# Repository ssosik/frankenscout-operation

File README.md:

# frankenscout-operation

Project files for a Trunk or Treat game: Arduino code, Kicad files, and general
design overview. Inspired by the game Operation with enhancements for multiple
faults before a game over, lots of gameplay sounds, and LED blinking patterns.

This was specifically for a Cub Scout Trunk or Treat event, so it's themed
around the 12 words of the Cub Scout Law: Trustworthy, Loyal, Helpful, Friendly,
Courteous, Kind, Obedient, Cheerful, Thrifty, Brave, Clean and Reverent.

## Components

- Arduino Nano: https://store.arduino.cc/products/arduino-nano
- MP3 Trigger: https://www.robertsonics.com/mp3-trigger
- Aux-in-compatible boombox speaker
- Custom PCB printed by PCBWay
- 3D printed bones
- 2x4s and 1/4" playwood (3'x4' playfield)
- Metal tongs + phone cord
- Metal HVAC foil tape for lining the edge of the bone boxes
- Big printout playfield
- random LEDs, wires, resistors, JST connectors, 74HC595 IC
- So much hot-glue

## Playthrough

LEDs quickly cycle through lighting up each of the 12 bone boxes one at a time,
randomly stopping on one.

Play a recording of one of our Scouts reciting the Scout Law word corresponding
to the lit up bone.

Start playing a randomly selected Halloween themed song.

The player uses the attached metal tongs to try to remove the lit up bone.

Each time the player touches the edge of the bone box, a randomly selected
warning sound is played. These sounds are recordings of our Scouts making spooky
sounds. Change the color of the nose to correspond to the warning level (green,
orange, blinking orange).

After playing the warning sound, resume playing the theme song.

If the player gets 3 warnings, the game is over. Turn the nose red and play a
short game over song. Start a new game.

If the player successfully removes the bone, trigger a separate switch to play
the win game song and have all the LEDs light up. Start a new game.

https://github.com/ssosik/frankenscout-operation/assets/11655703/48587010-1746-46a9-8444-a14359af3e6e

## Table

Nothing fancy, just some 2x4s screwed together. I added some legs to give some
space between the underside of the playfield and the ground below. Kids might
lean on the table, so make it strong.

## Playfield

1/4 inch plywood, roughly 3'x4'

## Picture

One of the other parents in our Den has access to a large color plot-printer at
work. I don't have any details on what it was.

I asked google to find me a picture in the appropriate theme, but I really
wanted to use something generated by Midjourney or Stable Diffusion.

## Cut-outs

Hope you're handy with a Jigsaw! I ended up cutting out wider holes on the
playfield, and then glued pieces to the underside with a more close-fitting bone
shape. These glued-on pieces are what form the edge of the bone boxes that are
crucial to the game. The inner edge of these holes is lined with metal foil tape
to complete the circuit through the metal tongs and back to the Arduino
interrupt pin.

The next time I do this I would consider 3D printing these pieces as well.

## Bone boxes

These were just roughly cut pieces of scrape 1/4 wood laminate, hot-glued
together. These don't really need to look nice, other than what can be seen
through the cut-outs from the top side of the play field.

I also hot-glued a small piece of stripboard with a few LEDs and a JST connector
into the corner of each bone box.

## Bones

One of the other parents in our Den did the 3D printings of the bones, so I
don't have the data files or other parameters for the prints. thingiverse.com
has so much to choose from.

## Electronics

The heart of this is an Arduino Nano.

It uses the Serial pins to talk to the MP3 Trigger.

The Nano only supports interrups on pins 2 and 3, so these are what I used for
the triggers for game faults and game wins.

I went overboard and used this as an opportunity to learn a bit about PCB
design, so I learned how to use Kicad to design the PCB and then ordered pieces
through PCBWay.

## Sounds

For music, I was able to find a good amount of stuff on the freemusicarchive.org
(e.g. Toccata and Fugue D Minor). With google, you can find so much more.

I used VLC and Audacity to convert these files so that the MP3 Trigger could
play them. I'm not sure if it was a bitrate thing or what, but some of the files
skipped during playback without convertion.

I just used my Mac to record the voices of our Scouts making spooky sounds and
reciting the words of the Scout Law. I used Audacity to cut up the audio files.

In the code I have a few separate start and stop indexes for the theme songs,
warn sounds, win songs, and lose songs. I use `random` to pick a random file in
the range between these indexes.

The MP3 Trigger use a micro SD card to for loading the MP3 files. These files
have a numeric prefix XXX that is used to index each file; i.e. a file named
`012-some-file.mp3` will be played when `t12` is sent over the Serial port to
the MP3 Trigger.

https://github.com/ssosik/frankenscout-operation/assets/11655703/ff72e206-2da6-4ab1-b68c-d1a4c78e1dd9

## Useful Links

- https://www.instructables.com/Multiplexing-with-Arduino-and-the-74HC595/
- https://docs.arduino.cc/tutorials/nano-every/uart
- https://learn.sparkfun.com/tutorials/mp3-trigger-hookup-guide-v24
- https://www.baldengineer.com/state-machine-with-enum-tutorial.html

## Improvements

- Use a magnetic switch (Normally Open) and magnets in the bones to trigger the
win events
- Normalize the sound files better to make the sound of our Scouts louder
- I'd like to add some kind of buzzer or solenoid popper to the game to give it
a bit more physical feedback

## Bugs

- The Arduino Nano that I'm using will temporarily ignore interrupt events every
so often, making the game seem unresponsive. After a bit of time, the interrupts
start working again, without a power cycle. I'm not sure what the source of this
is. I'm using Nano pins 2 and 3 in INPUT_PULLUP mode. If you have any ideas
please let me know!
- I'm not a C++ programmer, and coding in an event loop is tricky. There were
many bugs, and there are probably still a few.
- I ran out of time and wan't able to get the nose LEDs working properly. TODO

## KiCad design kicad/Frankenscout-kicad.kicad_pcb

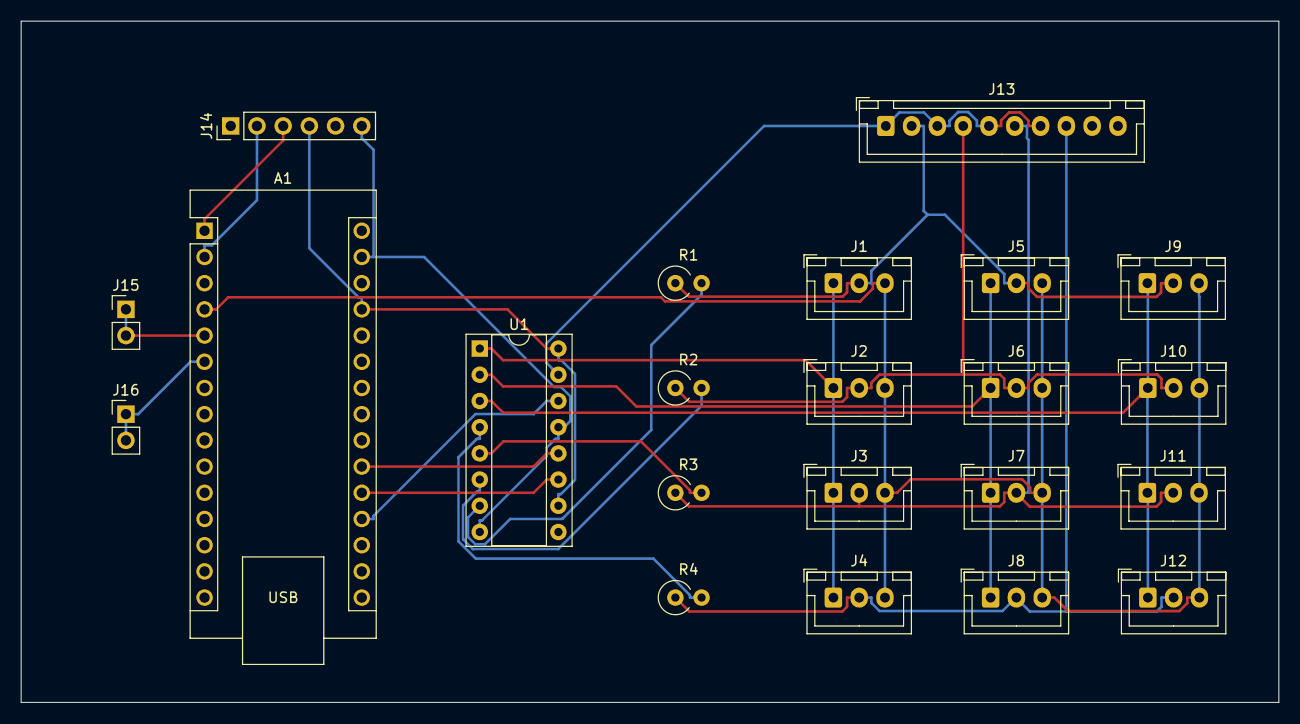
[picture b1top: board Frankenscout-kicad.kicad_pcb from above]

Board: 2 copper layers, 121.9 x 66.0 mm, 22 parts (0 on the bottom side), 22 nets.

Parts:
A1: Arduino_Nano_v3.x; Arduino_Nano
J1, J2, J3, J4, J5, J6, J7, J8, J9, J10, J11, J12: Conn_01x03_Socket; JST_XH_B3B-XH-A_1x03_P2.50mm_Vertical
J13: Conn_01x10_Socket; JST_XH_B10B-XH-A_1x10_P2.50mm_Vertical
J14: Conn_01x06_Socket; PinHeader_1x06_P2.54mm_Vertical
J15, J16: Conn_01x02_Socket; PinHeader_1x02_P2.54mm_Vertical
R1, R2, R3, R4: R; R_Axial_DIN0309_L9.0mm_D3.2mm_P2.54mm_Vertical
U1: 74HC595; DIP-16_W7.62mm_Socket

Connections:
unnamed: A1.27 (+5V), J14.4, U1.10 (~SRCLR), U1.16 (VCC)
unnamed: A1.19 (A0), U1.14 (SER)
unnamed: A1.20 (A1), U1.11 (SRCLK)
unnamed: A1.21 (A2), U1.12 (RCLK)
unnamed: A1.2 (D0/RX), J14.2
unnamed: A1.1 (D1/TX), J14.3
unnamed: A1.5 (D2), J15.1, J15.2
unnamed: A1.6 (D3), J16.1, J16.2
unnamed: J1.1, J2.1, J3.1, J4.1, U1.1 (QB)
unnamed: J1.2, J5.2, J9.2, J13.2, R1.1
unnamed: A1.4 (GND), J1.3, J2.3, J3.3, J4.3, J5.3, J6.3, J7.3, J8.3, J9.3, J10.3, J11.3, J12.3
unnamed: J5.1, J6.1, J7.1, J8.1, U1.2 (QC)
unnamed: J9.1, J10.1, J11.1, J12.1, U1.3 (QD)
unnamed: J2.2, J6.2, J10.2, J13.4, R2.1
unnamed: J3.2, J7.2, J11.2, J13.6, R3.1
unnamed: J4.2, J8.2, J12.2, J13.8, R4.1
unnamed: J13.1, J13.3, J13.5, J13.7, U1.15 (QA)
unnamed: A1.29 (GND), J14.6, U1.8 (GND), U1.13 (~OE)
unnamed: R4.2, U1.4 (QE)
unnamed: R3.2, U1.5 (QF)
unnamed: R2.2, U1.6 (QG)
unnamed: R1.2, U1.7 (QH)

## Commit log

2023-10-25 Initial add of README
2023-10-25 Add more to README
2023-10-25 Code drop game code
2023-10-25 Add KiCad files
2023-10-25 More README updates
2023-10-25 Add pics to README
2023-10-25 Add video to README.md
2023-10-25 Add video try 2 README.md
2023-10-25 Add one more video README.md
